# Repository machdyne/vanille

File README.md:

# Vanille Computer

Vanille is an FPGA computer designed by Lone Dynamics Corporation.

This repo will contain schematics, PCB layouts, pinouts, a 3D-printable case, example gateware and documentation.

Find more information on the [Vanille product page](https://machdyne.com/product/vanille-computer/).

## Programming Vanille

Vanille has a JTAG interface and ships with a [DFU bootloader](https://github.com/machdyne/tinydfu-bootloader) that allows the included flash [MMOD](https://machdyne.com/product/mmod) to be programmed over the USB-C port.

### DFU

The DFU bootloader is available for 5 seconds after power-on, issuing a DFU command during this period will stop the boot process until the DFU device is detached. If no command is received the boot process will continue and the user gateware will be loaded.

Install [dfu-util](http://dfu-util.sourceforge.net) (Debian/Ubuntu):

```
$ sudo apt install dfu-util
```

Update the user gateware on the flash MMOD:

```
$ sudo dfu-util -a 0 -D image.bit
```

Detach the DFU device and continue the boot process:

```
$ sudo dfu-util -a 0 -e
```

It is possible to update the bootloader itself using DFU but you shouldn't attempt this unless you have a JTAG programmer (or another method to program the MMOD) available, in case you need to restore the bootloader.

### JTAG

These examples assume you're using a "USB Blaster" JTAG cable, see the header pinout below. You will need to have [openFPGALoader](https://github.com/trabucayre/openFPGALoader) installed.

Program the configuration SRAM:

```
openFPGALoader -c usb-blaster image.bit
```

Program the flash MMOD:

```
openFPGALoader -f -c usb-blaster images/bootloader/tinydfu_vanille.bit
```

## Blinky 

Building the blinky example requires [Yosys](https://github.com/YosysHQ/yosys), [nextpnr-ecp5](https://github.com/YosysHQ/nextpnr) and [Project Trellis](https://github.com/YosysHQ/prjtrellis).

Assuming they are installed, you can simply type `make` to build the gateware, which will be written to output/blinky.bin. You can then use [openFPGALoader](https://github.com/trabucayre/openFPGALoader) or dfu-util to write the gateware to the device.

## Linux

See the [Kakao Linux](https://github.com/machdyne/kakao) repo for the latest instructions.

### Prebuilt Images

Prebuilt gateware capable of running Linux is available in the `images/v2` directory.

### Building Linux-capable Gateware

Please follow the setup instructions in the [linux-on-litex-vexriscv](https://github.com/litex-hub/linux-on-litex-vexriscv) repo and then:

1. Build the Linux-capable gateware:

```
$ cd linux-on-litex-vexriscv
$ ./make.py --board=vanille --dcache-size=64 --icache-size=64 --build
```

NOTE: This may fail, if so:

```
$ cd build/vanille/gateware
```

Edit `vanille.ys` and add the `-abc2` option as shown below:

```
synth_ecp5  -top vanille -abc2
```

Now run:

```
$ bash build_vanille.sh
```

2. Write the gateware to the MMOD using USB DFU:

```
$ sudo dfu-util -a 0 -D vanille.bit
```

3. Copy the device tree binary `../vanille.dtb` to a FAT-formatted MicroSD card.

## JTAG Header

The 3.3V JTAG header can be used to program the FPGA SRAM as well as the MMOD flash memory. It can also be used to provide power (5V) to the board.

```
1 2
3 4
5 6
```

| Pin | Signal |
| --- | ------ |
| 1 | TCK |
| 2 | TDI |
| 3 | TDO |
| 4 | TMS |
| 5 | 5V0 |
| 6 | GND |

## Board Revisions

| Revision | Notes |
| -------- | ----- |
| V0 | Initial prototype |
| V1 | Second prototype; fixes SRAM schematic error; adds LED |
| V2 | Initial production version; fixes another SRAM schematic error |

## License

The contents of this repo are released under the [Lone Dynamics Open License](LICENSE.md) with the following exceptions:

- The KiCad design files contain parts of the [kicad-pmod](https://github.com/mithro/kicad-pmod) library which is released under the [Apache License, Version 2.0](https://www.apache.org/licenses/LICENSE-2.0.html).

- The KiCad design files may contain symbols and footprints released under other licenses; please contact us if we've failed to give proper attribution.

Note: You can use these designs for commercial purposes but we ask that instead of producing exact clones, that you either replace our trademarks and logos with your own or add your own next to ours.

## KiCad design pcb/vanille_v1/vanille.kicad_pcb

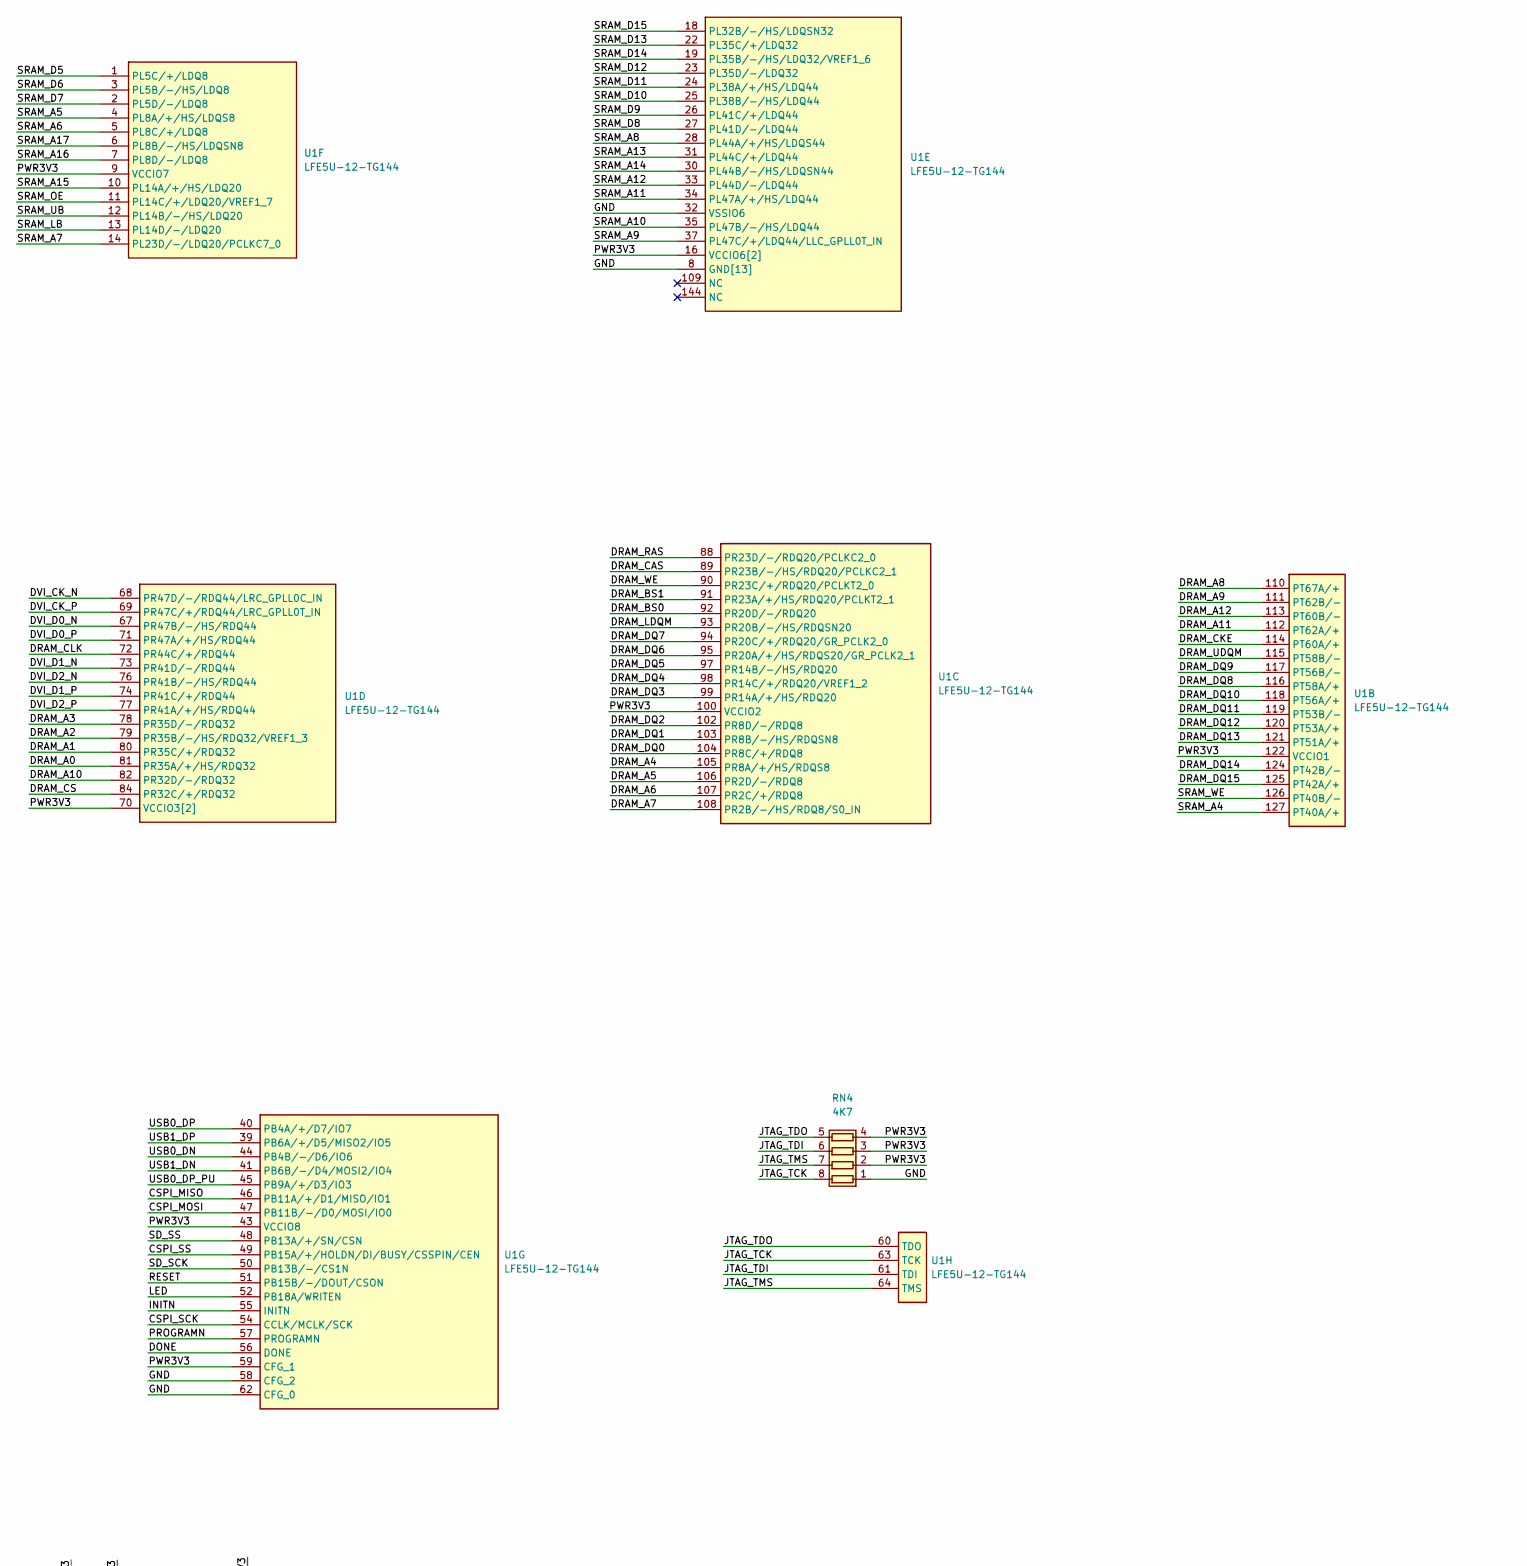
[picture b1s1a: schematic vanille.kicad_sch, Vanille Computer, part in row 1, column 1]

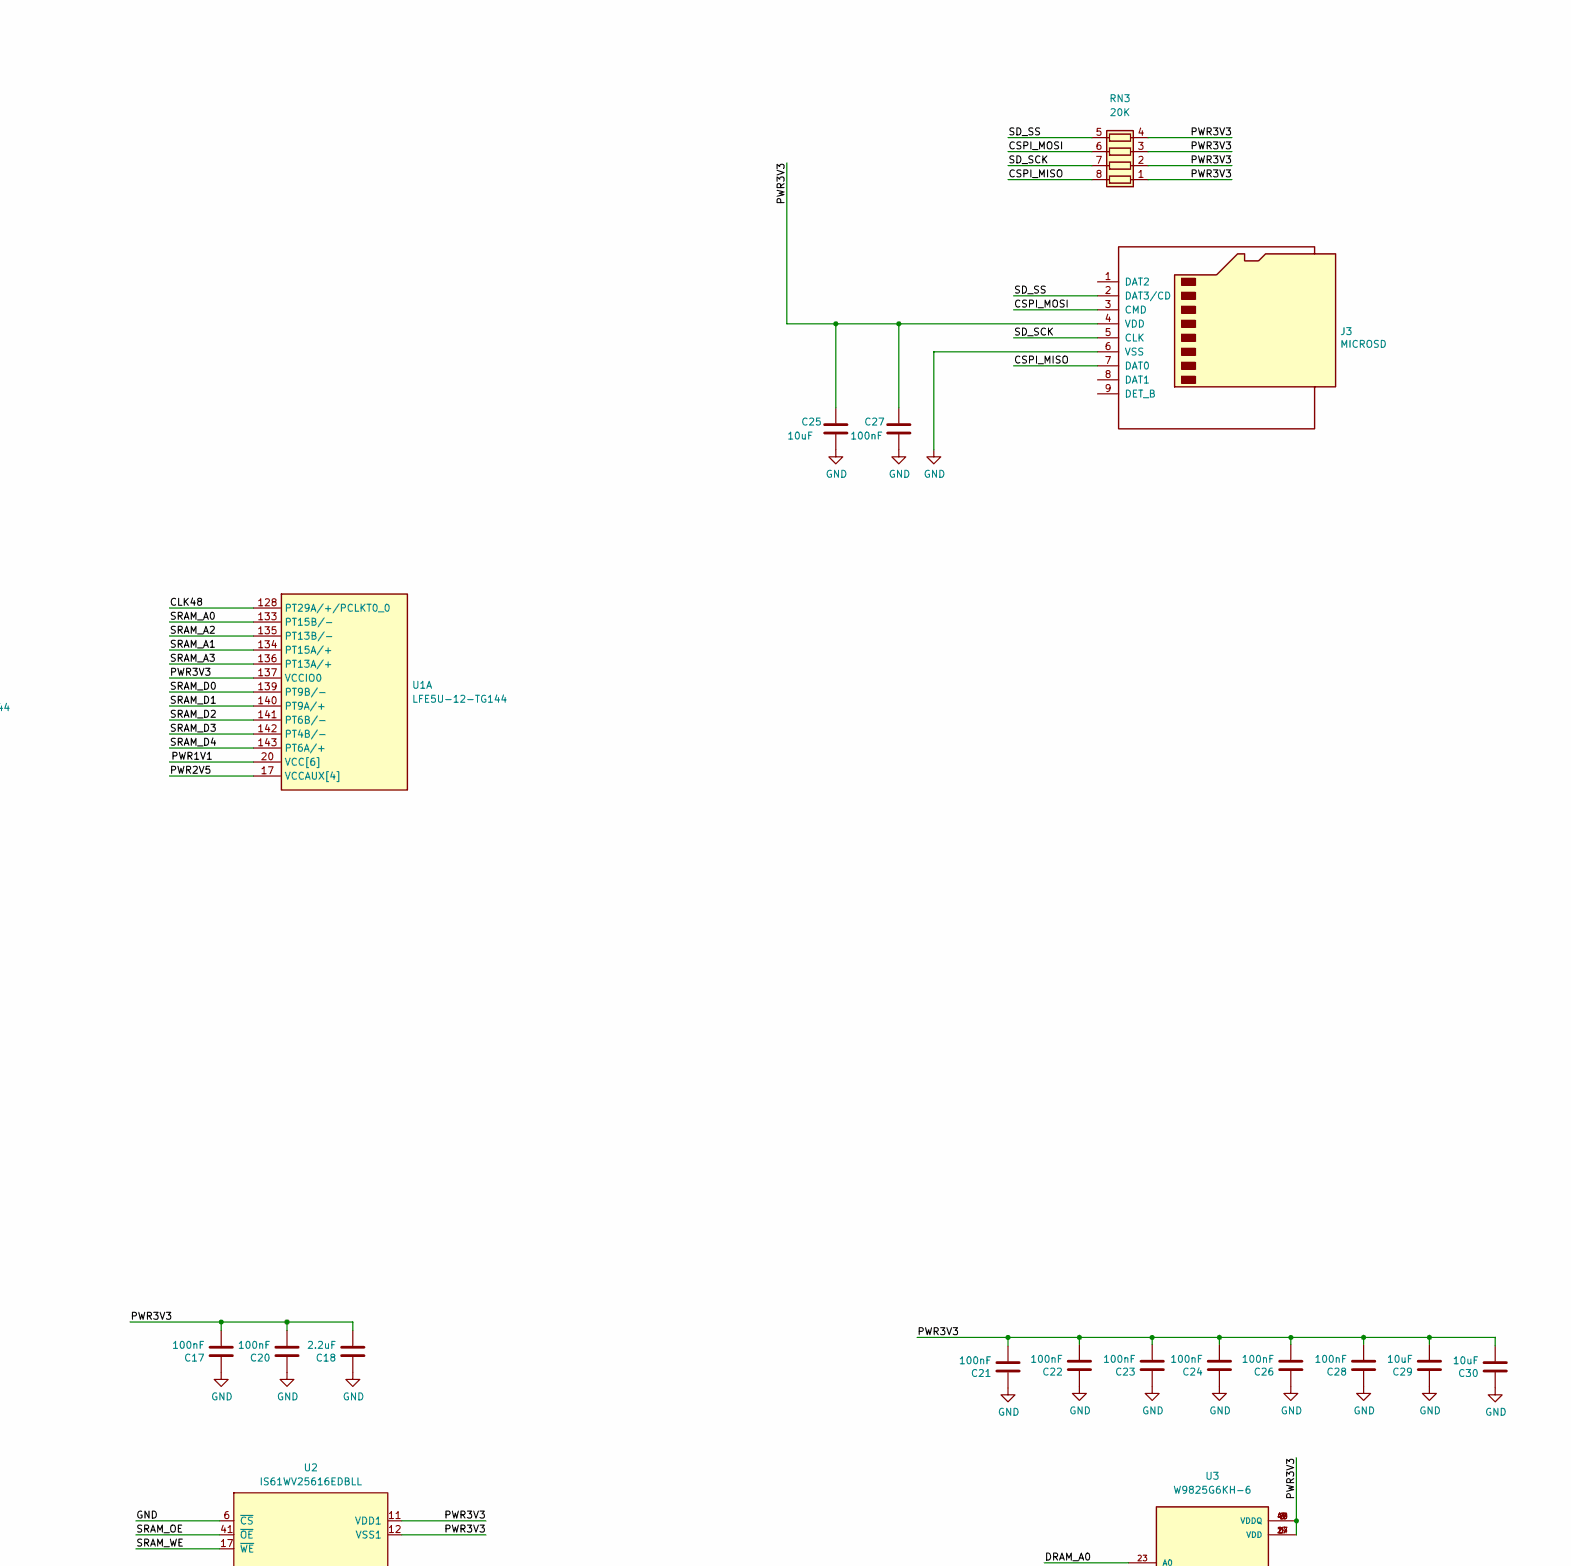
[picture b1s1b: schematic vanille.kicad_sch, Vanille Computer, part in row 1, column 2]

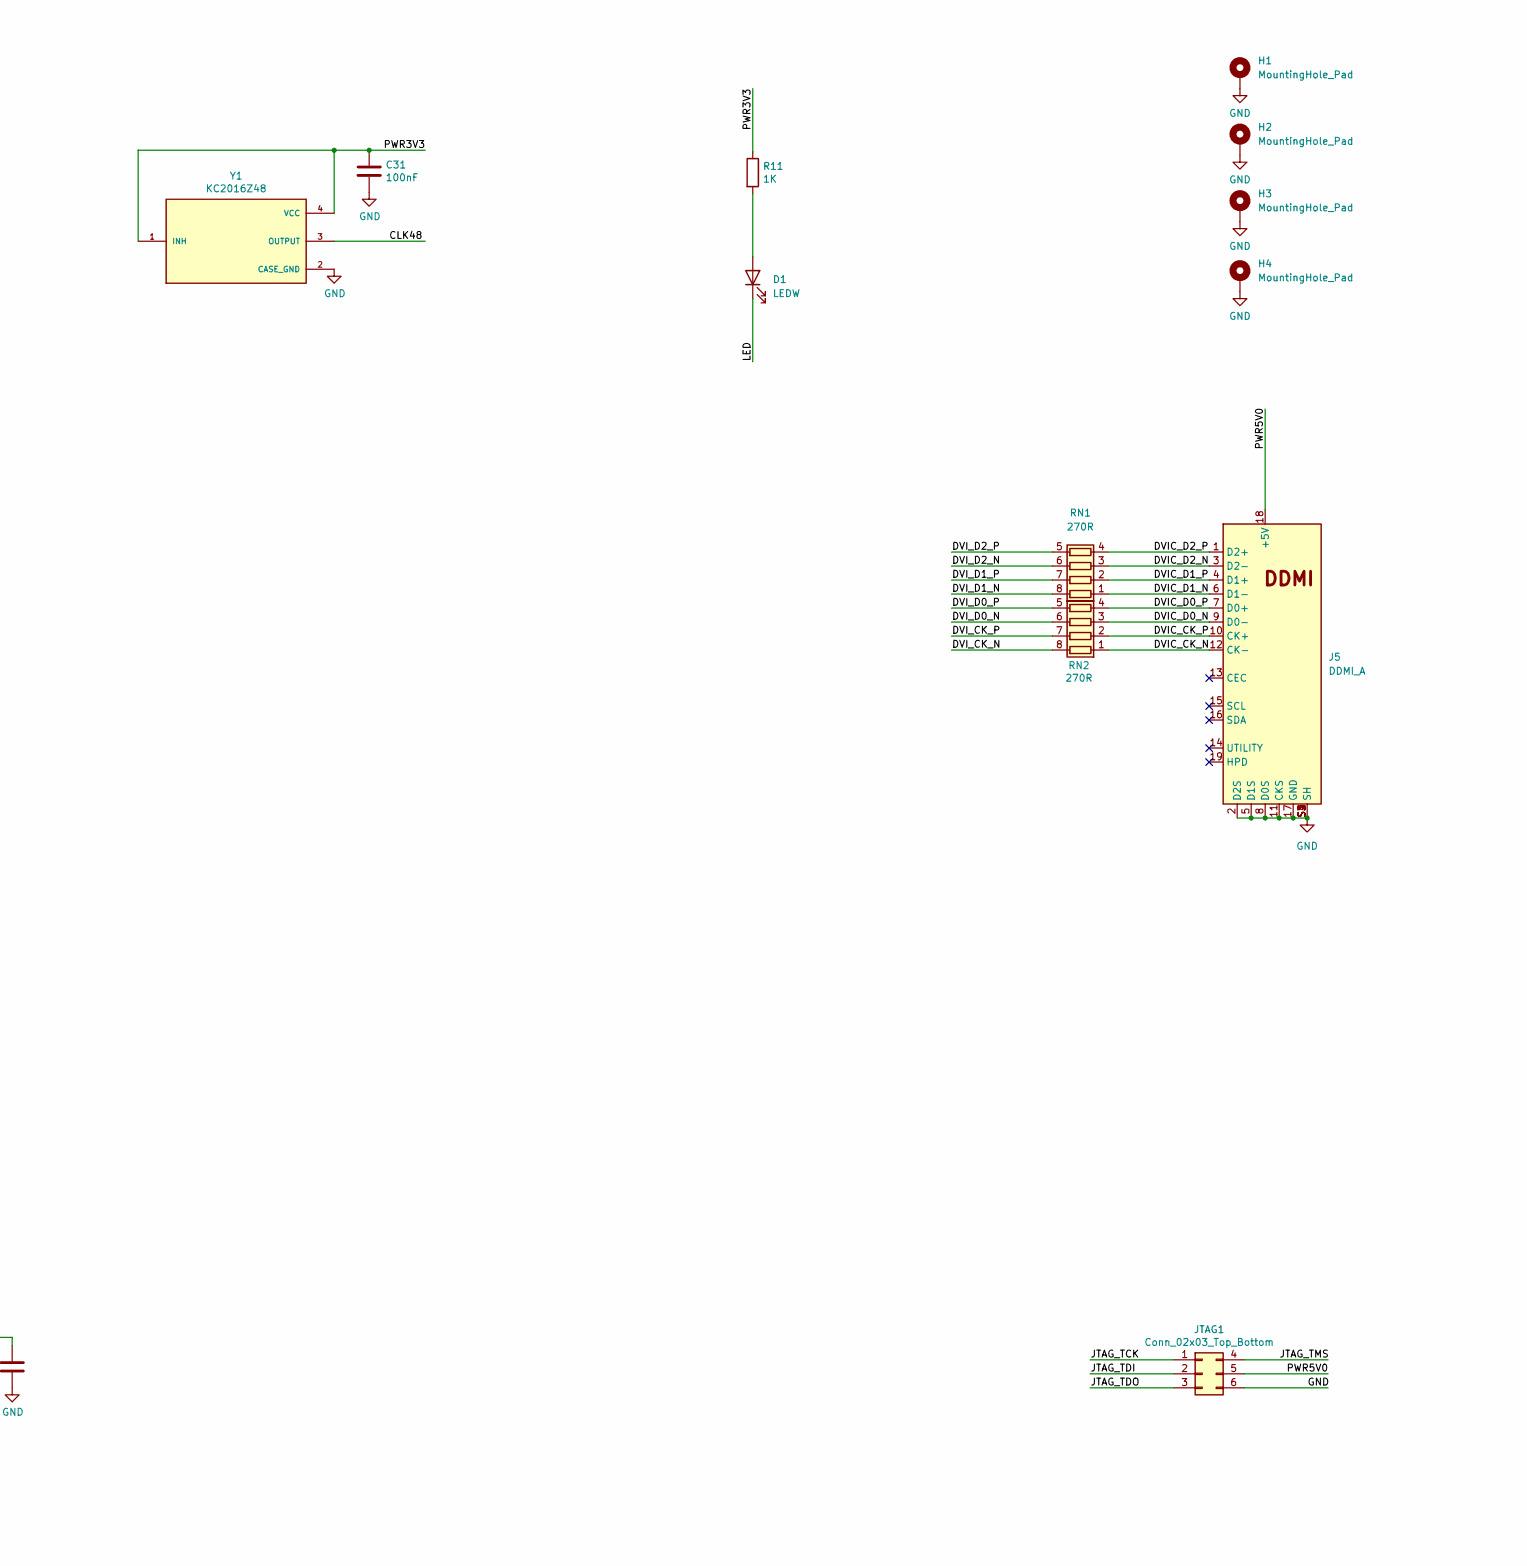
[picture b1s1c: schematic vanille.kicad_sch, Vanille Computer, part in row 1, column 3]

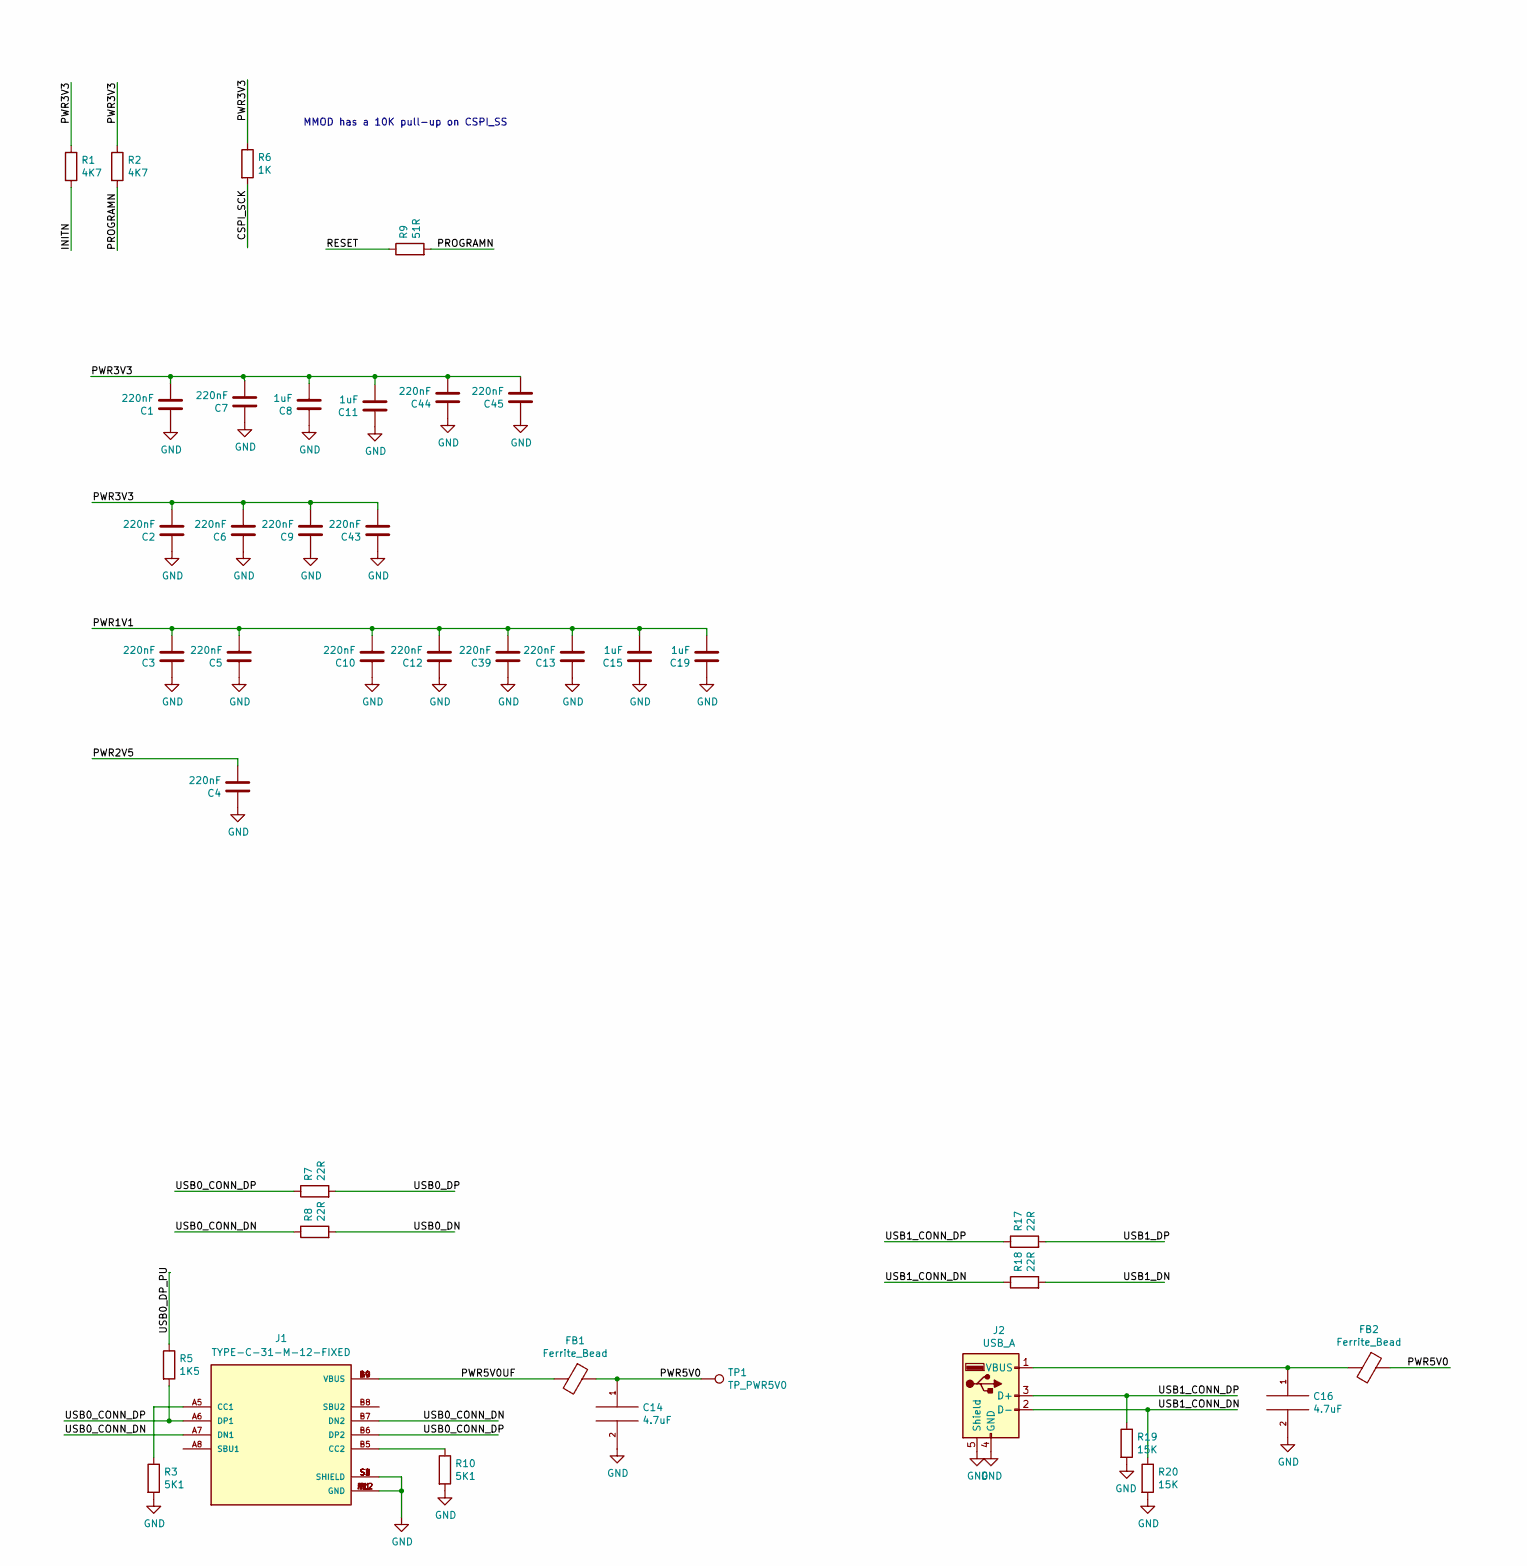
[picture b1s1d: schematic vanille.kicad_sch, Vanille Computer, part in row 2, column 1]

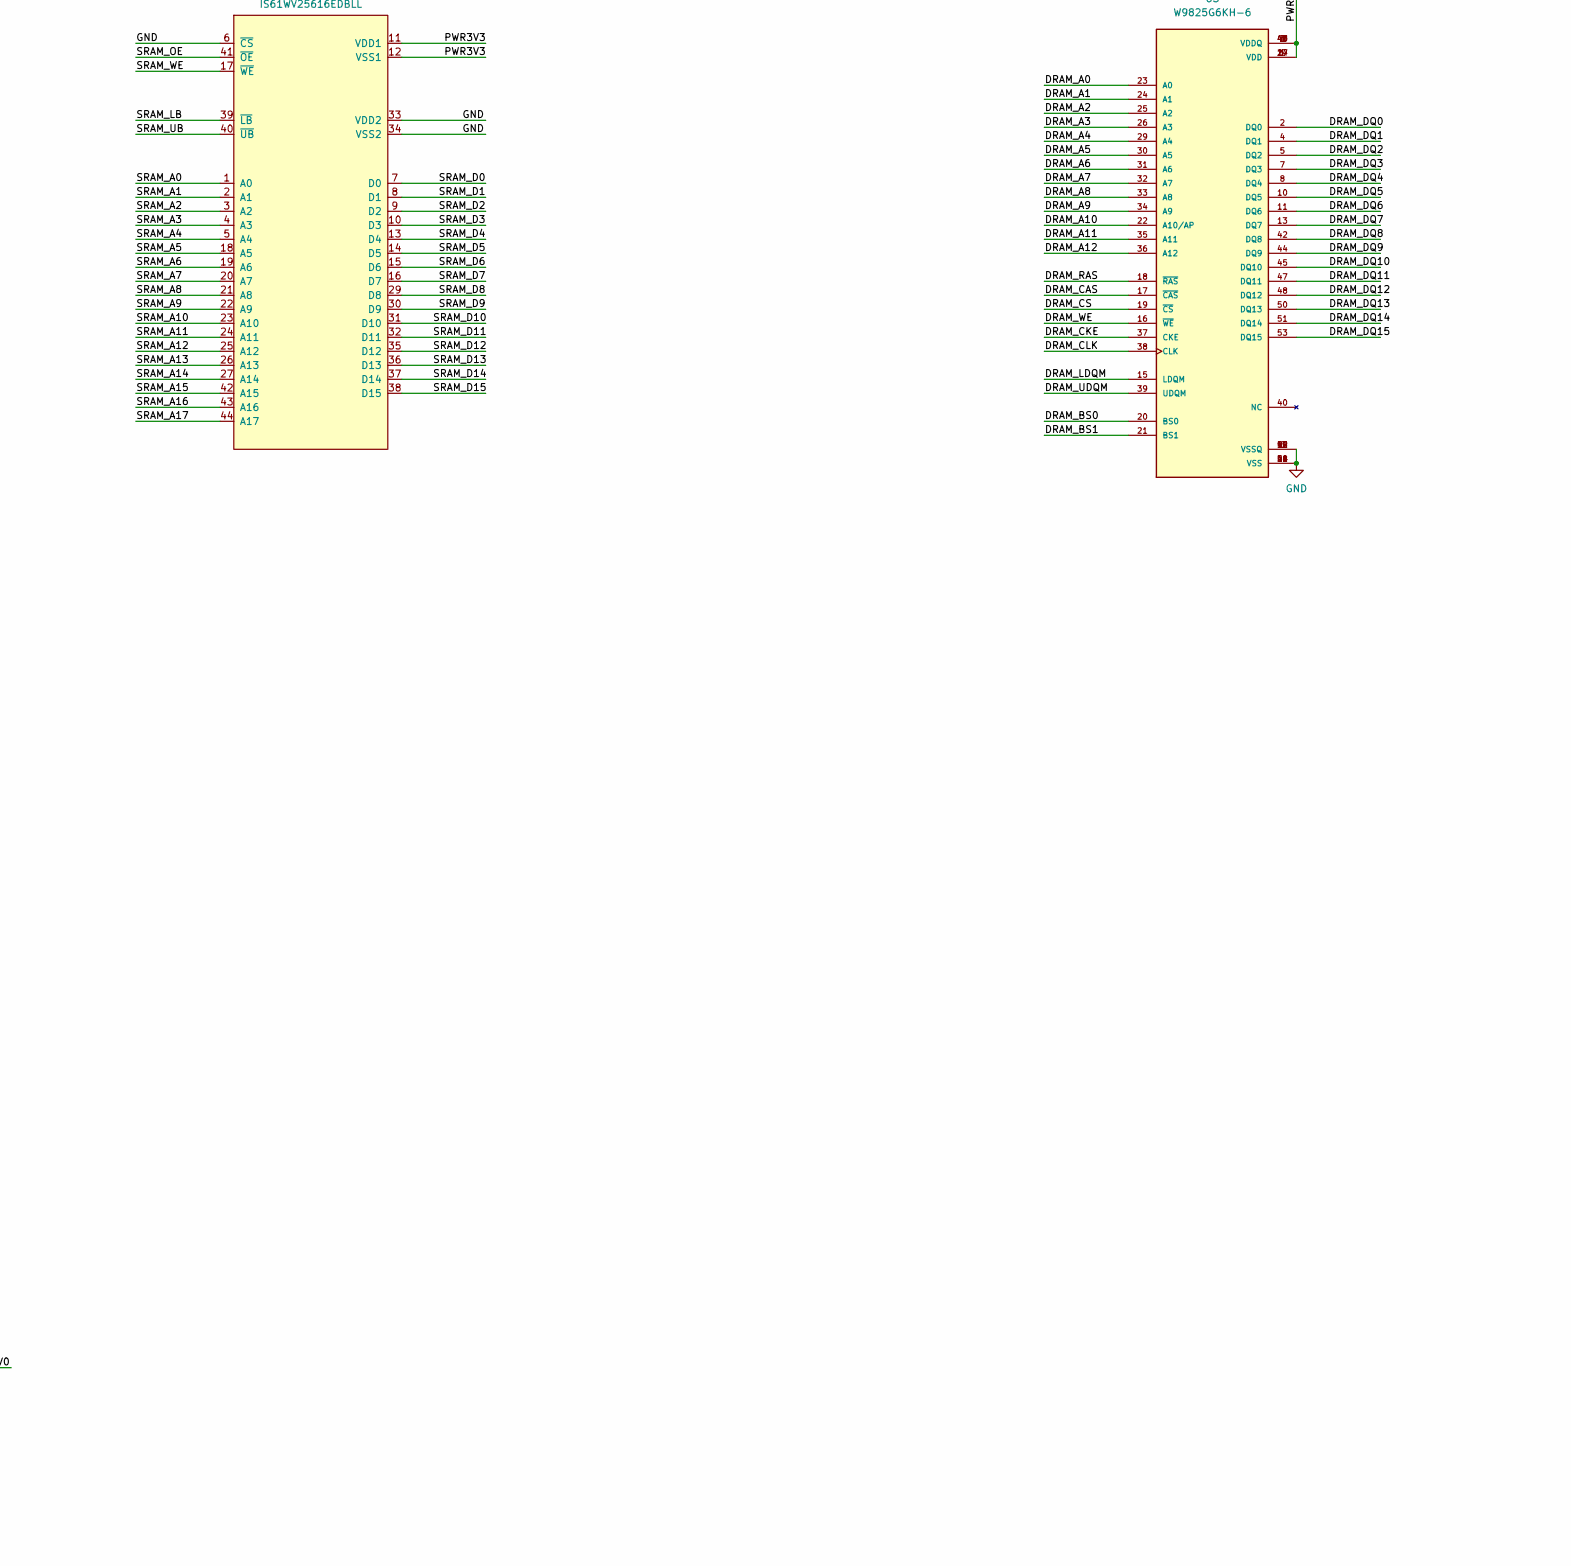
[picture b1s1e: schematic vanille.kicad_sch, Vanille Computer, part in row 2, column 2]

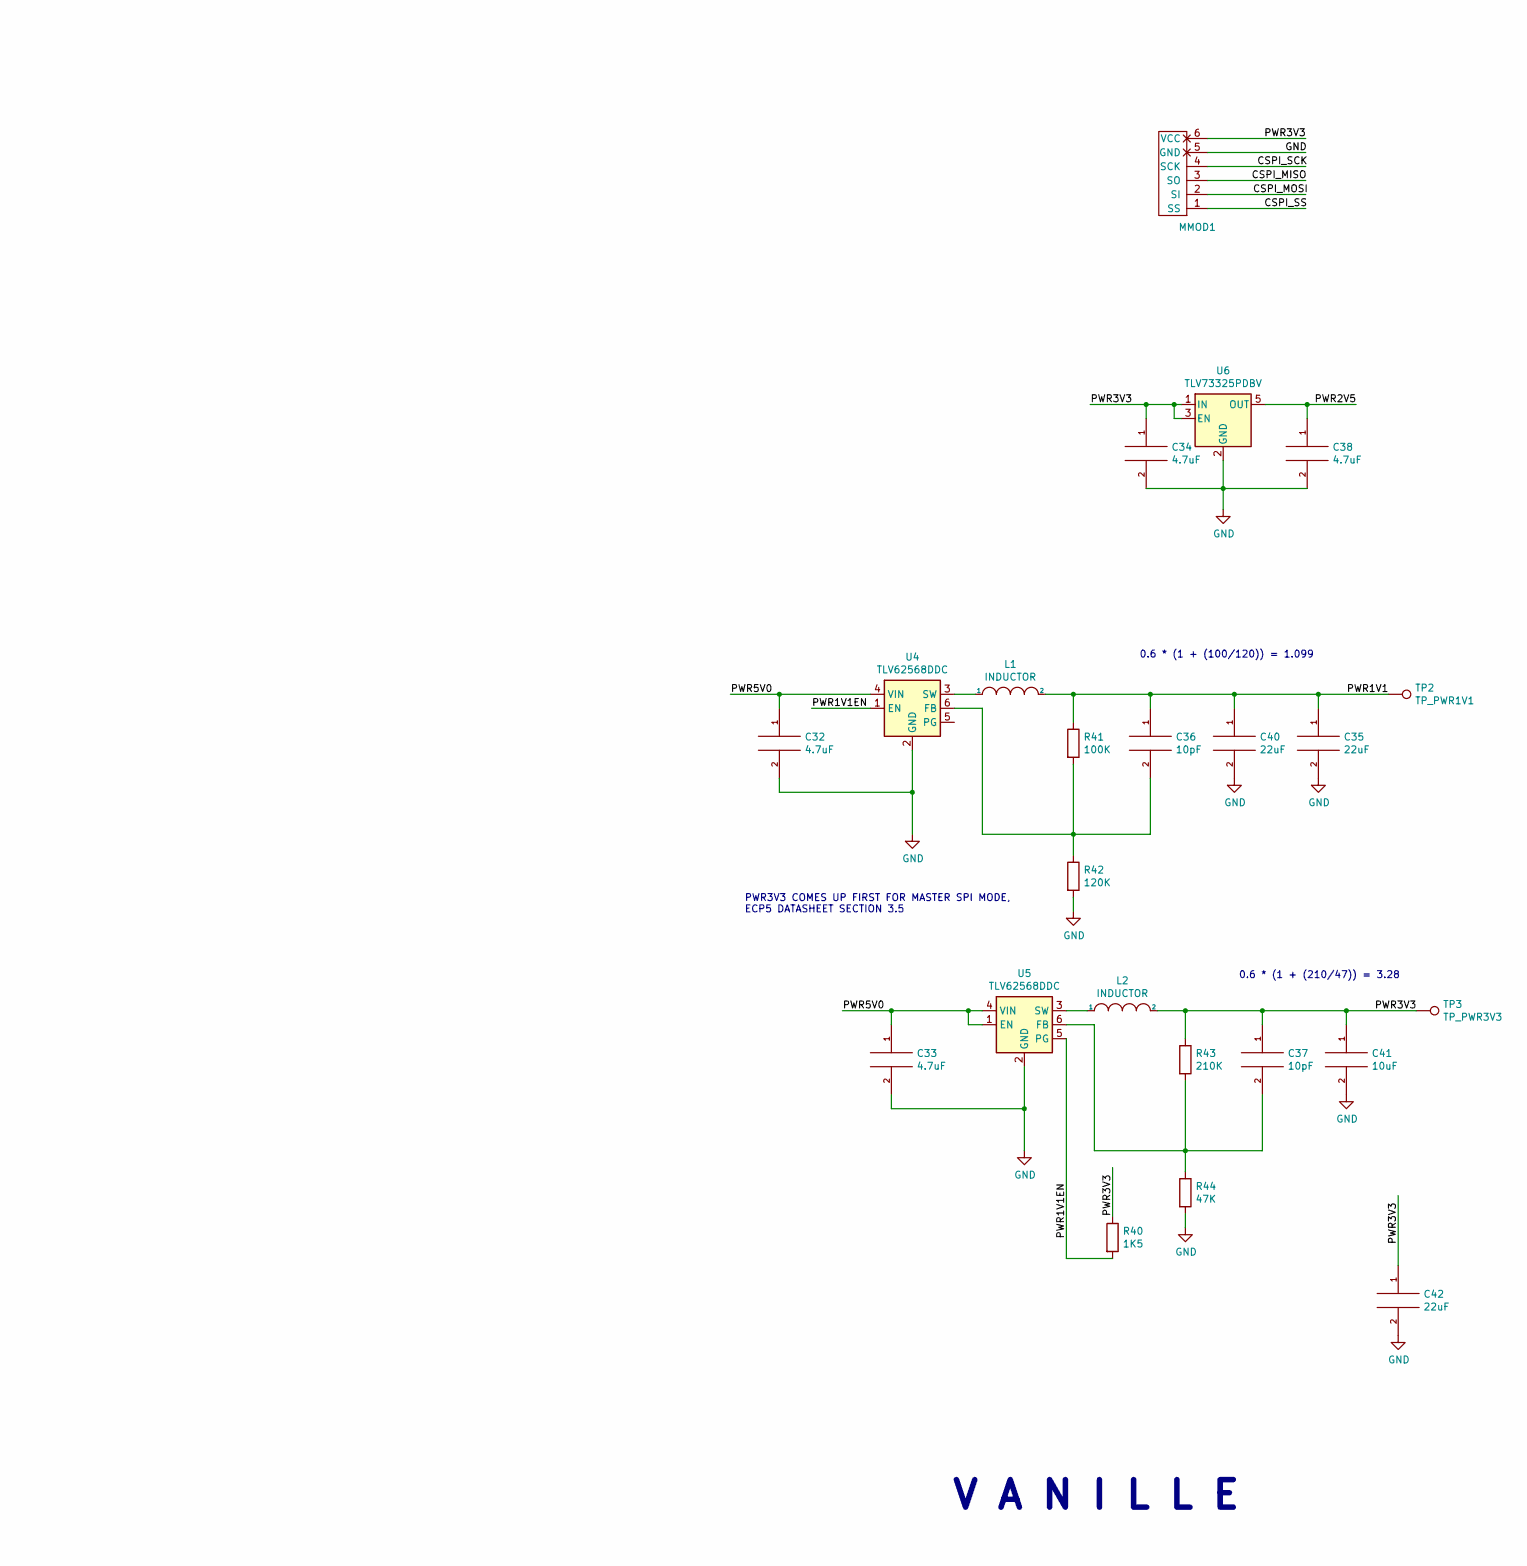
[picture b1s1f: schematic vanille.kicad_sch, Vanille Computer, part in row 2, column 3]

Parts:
C1, C2, C3, C4, C5, C6, C7, C9, C10, C12, C13, C39, C43, C44, C45: 220nF; C_0603_1608Metric
C8, C11, C15, C19: 1uF; C_0603_1608Metric
C14, C16, C32, C33, C34, C38: 4.7uF; C_0603_1608Metric
C17, C20, C21, C22, C23, C24, C26, C27, C28: 100nF; C_0603_1608Metric
C18: 2.2uF; C_0603_1608Metric
C25, C29, C30, C41: 10uF; C_0603_1608Metric
C31: 100nF; R_0603_1608Metric
C35, C40, C42: 22uF; C_0603_1608Metric
C36, C37: 10pF; C_0603_1608Metric
D1: LEDW; LED_0603_1608Metric
FB1, FB2: Ferrite_Bead; R_0603_1608Metric
H1, H2, H3, H4: MountingHole_Pad; MountingHole_3.2mm_M3_Pad
J1: TYPE-C-31-M-12-FIXED; USB_C_Receptacle_HRO_TYPE-C-31-M-12-BIG-PADS; PARTREV A
J2: USB_A; USB_A_Stewart_SS-52100-001_Horizontal
J3: MICROSD; SDCARD
J5: DDMI_A; HDMI_TE_1827059-3-FIXED
JTAG1: Conn_02x03_Top_Bottom; PinHeader_2x03_P2.54mm_Vertical
L1, L2: INDUCTOR; L_0805_2012Metric
MMOD1: PMOD-Device-x1-Type-2-SPI; MMOD_Host_Socket
R1, R2: 4K7; R_0603_1608Metric
R3, R10: 5K1; R_0603_1608Metric
R5, R40: 1K5; R_0603_1608Metric
R6, R11: 1K; R_0603_1608Metric
R7, R8, R17, R18: 22R; R_0603_1608Metric
R9: 51R; R_0603_1608Metric
R19, R20: 15K; R_0603_1608Metric
R41: 100K; R_0603_1608Metric
R42: 120K; R_0603_1608Metric
R43: 210K; R_0603_1608Metric
R44: 47K; R_0603_1608Metric
RN1, RN2: 270R; R_Array_Convex_4x0402
RN3: 20K; R_Array_Convex_4x0402
RN4: 4K7; R_Array_Convex_4x0402
TP1: TP_PWR5V0; TestPoint_THTPad_D1.0mm_Drill0.5mm
TP2: TP_PWR1V1; TestPoint_THTPad_D1.0mm_Drill0.5mm
TP3: TP_PWR3V3; TestPoint_THTPad_D1.0mm_Drill0.5mm
U1: LFE5U-12-TG144
U2: IS61WV25616EDBLL; TSOP-II-44_10.16x18.41mm_P0.8mm
U3: W9825G6KH-6; SOP80P1176X120-54N; PARTREV A05
U4, U5: TLV62568DDC; SOT-23-6
U6: TLV73325PDBV; SOT-23-5
Y1: KC2016Z48; OSC_KC2016Z13.5600C1KX00; PARTREV November 2020

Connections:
/CLK48: U1.128 (PT29A/+/PCLKT0_0), Y1.3 (OUTPUT)
/CSPI_MISO: J3.7 (DAT0), MMOD1.3 (SO), RN3.8 (R1.2), U1.46 (PB11A/+/D1/MISO/IO1)
/CSPI_MOSI: J3.3 (CMD), MMOD1.2 (SI), RN3.6 (R3.2), U1.47 (PB11B/-/D0/MOSI/IO0)
/CSPI_SCK: MMOD1.4 (SCK), R6.2, U1.54 (CCLK/MCLK/SCK)
/CSPI_SS: MMOD1.1 (SS), U1.49 (PB15A/+/HOLDN/DI/BUSY/CSSPIN/CEN)
/DONE: U1.56 (DONE)
/DRAM_A0: U1.81 (PR35A/+/HS/RDQ32), U3.23 (A0)
/DRAM_A1: U1.80 (PR35C/+/RDQ32), U3.24 (A1)
/DRAM_A2: U1.79 (PR35B/-/HS/RDQ32/VREF1_3), U3.25 (A2)
/DRAM_A3: U1.78 (PR35D/-/RDQ32), U3.26 (A3)
/DRAM_A4: U1.105 (PR8A/+/HS/RDQS8), U3.29 (A4)
/DRAM_A5: U1.106 (PR2D/-/RDQ8), U3.30 (A5)
/DRAM_A6: U1.107 (PR2C/+/RDQ8), U3.31 (A6)
/DRAM_A7: U1.108 (PR2B/-/HS/RDQ8/S0_IN), U3.32 (A7)
/DRAM_A8: U1.110 (PT67A/+), U3.33 (A8)
/DRAM_A9: U1.111 (PT62B/-), U3.34 (A9)
/DRAM_A10: U1.82 (PR32D/-/RDQ32), U3.22 (A10/AP)
/DRAM_A11: U1.112 (PT62A/+), U3.35 (A11)
/DRAM_A12: U1.113 (PT60B/-), U3.36 (A12)
/DRAM_BS0: U1.92 (PR20D/-/RDQ20), U3.20 (BS0)
/DRAM_BS1: U1.91 (PR23A/+/HS/RDQ20/PCLKT2_1), U3.21 (BS1)
/DRAM_CAS: U1.89 (PR23B/-/HS/RDQ20/PCLKC2_1), U3.17 (~CAS)
/DRAM_CKE: U1.114 (PT60A/+), U3.37 (CKE)
/DRAM_CLK: U1.72 (PR44C/+/RDQ44), U3.38 (CLK)
/DRAM_CS: U1.84 (PR32C/+/RDQ32), U3.19 (~CS)
/DRAM_DQ0: U1.104 (PR8C/+/RDQ8), U3.2 (DQ0)
/DRAM_DQ1: U1.103 (PR8B/-/HS/RDQSN8), U3.4 (DQ1)
/DRAM_DQ2: U1.102 (PR8D/-/RDQ8), U3.5 (DQ2)
/DRAM_DQ3: U1.99 (PR14A/+/HS/RDQ20), U3.7 (DQ3)
/DRAM_DQ4: U1.98 (PR14C/+/RDQ20/VREF1_2), U3.8 (DQ4)
/DRAM_DQ5: U1.97 (PR14B/-/HS/RDQ20), U3.10 (DQ5)
/DRAM_DQ6: U1.95 (PR20A/+/HS/RDQS20/GR_PCLK2_1), U3.11 (DQ6)
/DRAM_DQ7: U1.94 (PR20C/+/RDQ20/GR_PCLK2_0), U3.13 (DQ7)
/DRAM_DQ8: U1.116 (PT58A/+), U3.42 (DQ8)
/DRAM_DQ9: U1.117 (PT56B/-), U3.44 (DQ9)
/DRAM_DQ10: U1.118 (PT56A/+), U3.45 (DQ10)
/DRAM_DQ11: U1.119 (PT53B/-), U3.47 (DQ11)
/DRAM_DQ12: U1.120 (PT53A/+), U3.48 (DQ12)
/DRAM_DQ13: U1.121 (PT51A/+), U3.50 (DQ13)
/DRAM_DQ14: U1.124 (PT42B/-), U3.51 (DQ14)
/DRAM_DQ15: U1.125 (PT42A/+), U3.53 (DQ15)
/DRAM_LDQM: U1.93 (PR20B/-/HS/RDQSN20), U3.15 (LDQM)
/DRAM_RAS: U1.88 (PR23D/-/RDQ20/PCLKC2_0), U3.18 (~RAS)
/DRAM_UDQM: U1.115 (PT58B/-), U3.39 (UDQM)
/DRAM_WE: U1.90 (PR23C/+/RDQ20/PCLKT2_0), U3.16 (~WE)
/DVIC_CK_N: J5.12 (CK-), RN2.1 (R1.1)
/DVIC_CK_P: J5.10 (CK+), RN2.2 (R2.1)
/DVIC_D0_N: J5.9 (D0-), RN2.3 (R3.1)
/DVIC_D0_P: J5.7 (D0+), RN2.4 (R4.1)
/DVIC_D1_N: J5.6 (D1-), RN1.1 (R1.1)
/DVIC_D1_P: J5.4 (D1+), RN1.2 (R2.1)
/DVIC_D2_N: J5.3 (D2-), RN1.3 (R3.1)
/DVIC_D2_P: J5.1 (D2+), RN1.4 (R4.1)
/DVI_CK_N: RN2.8 (R1.2), U1.68 (PR47D/-/RDQ44/LRC_GPLL0C_IN)
/DVI_CK_P: RN2.7 (R2.2), U1.69 (PR47C/+/RDQ44/LRC_GPLL0T_IN)
/DVI_D0_N: RN2.6 (R3.2), U1.67 (PR47B/-/HS/RDQ44)
/DVI_D0_P: RN2.5 (R4.2), U1.71 (PR47A/+/HS/RDQ44)
/DVI_D1_N: RN1.8 (R1.2), U1.73 (PR41D/-/RDQ44)
/DVI_D1_P: RN1.7 (R2.2), U1.74 (PR41C/+/RDQ44)
/DVI_D2_N: RN1.6 (R3.2), U1.76 (PR41B/-/HS/RDQ44)
/DVI_D2_P: RN1.5 (R4.2), U1.77 (PR41A/+/HS/RDQ44)
/INITN: R1.2, U1.55 (INITN)
/JTAG_TCK: JTAG1.1, RN4.8 (R1.2), U1.63 (TCK)
/JTAG_TDI: JTAG1.2, RN4.6 (R3.2), U1.61 (TDI)
/JTAG_TDO: JTAG1.3, RN4.5 (R4.2), U1.60 (TDO)
/JTAG_TMS: JTAG1.4, RN4.7 (R2.2), U1.64 (TMS)
/LED: D1.1 (K), U1.52 (PB18A/WRITEN)
/PROGRAMN: R2.2, R9.2, U1.57 (PROGRAMN)
/PWR1V1: C3.2, C5.2, C10.2, C12.2, C13.2, C15.2, C19.2, C35.1, C36.1, C39.2, C40.1, L1.2, R41.1, TP2.1, U1.20 (VCC[6]), U1.29 (VCC[6]), U1.38 (VCC[6]), U1.66 (VCC[6]), U1.83 (VCC[6]), U1.130 (VCC[6])
/PWR1V1EN: R40.2, U4.1 (EN), U5.5 (PG)
/PWR2V5: C4.2, C38.1, U1.17 (VCCAUX[4]), U1.53 (VCCAUX[4]), U1.96 (VCCAUX[4]), U1.132 (VCCAUX[4]), U6.5 (OUT)
/PWR3V3: C1.2, C2.2, C6.2, C7.2, C8.2, C9.2, C11.2, C17.2, C18.2, C20.2, C21.2, C22.2, C23.2, C24.2, C25.1, C26.2, C27.1, C28.2, C29.2, C30.2, C31.1, C34.1, C37.1, C41.1, C42.1, C43.2, C44.2, C45.2, J3.4 (VDD), L2.2, MMOD1.6 (VCC), R1.1, R2.1, R6.1, R11.1, R40.1, R43.1, RN3.1 (R1.1), RN3.2 (R2.1), RN3.3 (R3.1), RN3.4 (R4.1), RN4.2 (R2.1), RN4.3 (R3.1), RN4.4 (R4.1), TP3.1, U1.9 (VCCIO7), U1.16 (VCCIO6[2]), U1.36 (VCCIO6[2]), U1.43 (VCCIO8), U1.59 (CFG_1), U1.70 (VCCIO3[2]), U1.86 (VCCIO3[2]), U1.100 (VCCIO2), U1.122 (VCCIO1), U1.137 (VCCIO0), U2.11 (VDD1), U2.12 (VSS1), U3.1 (VDD), U3.3 (VDDQ), U3.9 (VDDQ), U3.14 (VDD), U3.27 (VDD), U3.43 (VDDQ), U3.49 (VDDQ), U6.1 (IN), U6.3 (EN), Y1.1 (INH), Y1.4 (VCC)
/PWR5V0: C14.1, C32.1, C33.1, FB1.1, FB2.1, J5.18 (+5V), JTAG1.5, TP1.1, U4.4 (VIN), U5.1 (EN), U5.4 (VIN)
/PWR5V0UF: FB1.2, J1.A4 (VBUS), J1.A9 (VBUS), J1.B4 (VBUS), J1.B9 (VBUS)
/RESET: R9.1, U1.51 (PB15B/-/DOUT/CSON)
/SD_SCK: J3.5 (CLK), RN3.7 (R2.2), U1.50 (PB13B/-/CS1N)
/SD_SS: J3.2 (DAT3/CD), RN3.5 (R4.2), U1.48 (PB13A/+/SN/CSN)
/SRAM_A0: U1.133 (PT15B/-), U2.1 (A0)
/SRAM_A1: U1.134 (PT15A/+), U2.2 (A1)
/SRAM_A2: U1.135 (PT13B/-), U2.3 (A2)
/SRAM_A3: U1.136 (PT13A/+), U2.4 (A3)
/SRAM_A4: U1.127 (PT40A/+), U2.5 (A4)
/SRAM_A5: U1.4 (PL8A/+/HS/LDQS8), U2.18 (A5)
/SRAM_A6: U1.5 (PL8C/+/LDQ8), U2.19 (A6)
/SRAM_A7: U1.14 (PL23D/-/LDQ20/PCLKC7_0), U2.20 (A7)
/SRAM_A8: U1.28 (PL44A/+/HS/LDQS44), U2.21 (A8)
/SRAM_A9: U1.37 (PL47C/+/LDQ44/LLC_GPLL0T_IN), U2.22 (A9)
/SRAM_A10: U1.35 (PL47B/-/HS/LDQ44), U2.23 (A10)
/SRAM_A11: U1.34 (PL47A/+/HS/LDQ44), U2.24 (A11)
/SRAM_A12: U1.33 (PL44D/-/LDQ44), U2.25 (A12)
/SRAM_A13: U1.31 (PL44C/+/LDQ44), U2.26 (A13)
/SRAM_A14: U1.30 (PL44B/-/HS/LDQSN44), U2.27 (A14)
/SRAM_A15: U1.10 (PL14A/+/HS/LDQ20), U2.42 (A15)
/SRAM_A16: U1.7 (PL8D/-/LDQ8), U2.43 (A16)
/SRAM_A17: U1.6 (PL8B/-/HS/LDQSN8), U2.44 (A17)
/SRAM_D0: U1.139 (PT9B/-), U2.7 (D0)
/SRAM_D1: U1.140 (PT9A/+), U2.8 (D1)
/SRAM_D2: U1.141 (PT6B/-), U2.9 (D2)
/SRAM_D3: U1.142 (PT4B/-), U2.10 (D3)
/SRAM_D4: U1.143 (PT6A/+), U2.13 (D4)
/SRAM_D5: U1.1 (PL5C/+/LDQ8), U2.14 (D5)
/SRAM_D6: U1.3 (PL5B/-/HS/LDQ8), U2.15 (D6)
/SRAM_D7: U1.2 (PL5D/-/LDQ8), U2.16 (D7)
/SRAM_D8: U1.27 (PL41D/-/LDQ44), U2.29 (D8)
/SRAM_D9: U1.26 (PL41C/+/LDQ44), U2.30 (D9)
/SRAM_D10: U1.25 (PL38B/-/HS/LDQ44), U2.31 (D10)
/SRAM_D11: U1.24 (PL38A/+/HS/LDQ44), U2.32 (D11)
/SRAM_D12: U1.23 (PL35D/-/LDQ32), U2.35 (D12)
/SRAM_D13: U1.22 (PL35C/+/LDQ32), U2.36 (D13)
/SRAM_D14: U1.19 (PL35B/-/HS/LDQ32/VREF1_6), U2.37 (D14)
/SRAM_D15: U1.18 (PL32B/-/HS/LDQSN32), U2.38 (D15)
/SRAM_LB: U1.13 (PL14D/-/LDQ20), U2.39 (~LB)
/SRAM_OE: U1.11 (PL14C/+/LDQ20/VREF1_7), U2.41 (~OE)
/SRAM_UB: U1.12 (PL14B/-/HS/LDQ20), U2.40 (~UB)
/SRAM_WE: U1.126 (PT40B/-), U2.17 (~WE)
/USB0_CONN_DN: J1.A7 (DN1), J1.B7 (DN2), R8.1
/USB0_CONN_DP: J1.A6 (DP1), J1.B6 (DP2), R5.2, R7.1
/USB0_DN: R8.2, U1.44 (PB4B/-/D6/IO6)
/USB0_DP: R7.2, U1.40 (PB4A/+/D7/IO7)
/USB0_DP_PU: R5.1, U1.45 (PB9A/+/D3/IO3)
/USB1_CONN_DN: J2.2 (D-), R18.1, R20.1
/USB1_CONN_DP: J2.3 (D+), R17.1, R19.1
/USB1_DN: R18.2, U1.41 (PB6B/-/D4/MOSI2/IO4)
/USB1_DP: R17.2, U1.39 (PB6A/+/D5/MISO2/IO5)
GND: C1.1, C2.1, C3.1, C4.1, C5.1, C6.1, C7.1, C8.1, C9.1, C10.1, C11.1, C12.1, C13.1, C14.2, C15.1, C16.2, C17.1, C18.1, C19.1, C20.1, C21.1, C22.1, C23.1, C24.1, C25.2, C26.1, C27.2, C28.1, C29.1, C30.1, C31.2, C32.2, C33.2, C34.2, C35.2, C38.2, C39.1, C40.2, C41.2, C42.2, C43.1, C44.1, C45.1, H1.1, H2.1, H3.1, H4.1, J1.A1 (GND), J1.A12 (GND), J1.B1 (GND), J1.B12 (GND), J1.S1 (SHIELD), J1.S2 (SHIELD), J1.S3 (SHIELD), J1.S4 (SHIELD), J2.4 (GND), J2.5 (Shield), J3.6 (VSS), J5.2 (D2S), J5.5 (D1S), J5.8 (D0S), J5.11 (CKS), J5.17 (GND), J5.S1 (SH), J5.S2 (SH), J5.S3 (SH), J5.S4 (SH), JTAG1.6, MMOD1.5 (GND), R3.2, R10.2, R19.2, R20.2, R42.2, R44.2, RN4.1 (R1.1), U1.8 (GND[13]), U1.15 (GND[13]), U1.21 (GND[13]), U1.32 (VSSIO6), U1.42 (GND[13]), U1.58 (CFG_2), U1.62 (CFG_0), U1.65 (GND[13]), U1.75 (GND[13]), U1.85 (GND[13]), U1.87 (GND[13]), U1.101 (GND[13]), U1.123 (GND[13]), U1.129 (GND[13]), U1.131 (GND[13]), U1.138 (GND[13]), U2.6 (~CS), U2.33 (VDD2), U2.34 (VSS2), U3.6 (VSSQ), U3.12 (VSSQ), U3.28 (VSS), U3.41 (VSS), U3.46 (VSSQ), U3.52 (VSSQ), U3.54 (VSS), U4.2 (GND), U5.2 (GND), U6.2 (GND), Y1.2 (CASE_GND)
unnamed: C16.1, FB2.2, J2.1 (VBUS)
unnamed: C36.2, R41.2, R42.1, U4.6 (FB)
unnamed: C37.2, R43.2, R44.1, U5.6 (FB)
unnamed: D1.2 (A), R11.2
unnamed: J1.A5 (CC1), R3.1
unnamed: J1.B5 (CC2), R10.1
unnamed: L1.1, U4.3 (SW)
unnamed: L2.1, U5.3 (SW)

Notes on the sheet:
V A N I L L E
PWR3V3 COMES UP FIRST FOR MASTER SPI MODE, ECP5 DATASHEET SECTION 3.5
0.6 * (1 + (210/47)) = 3.28
MMOD has a 10K pull-up on CSPI_SS
0.6 * (1 + (100/120)) = 1.099

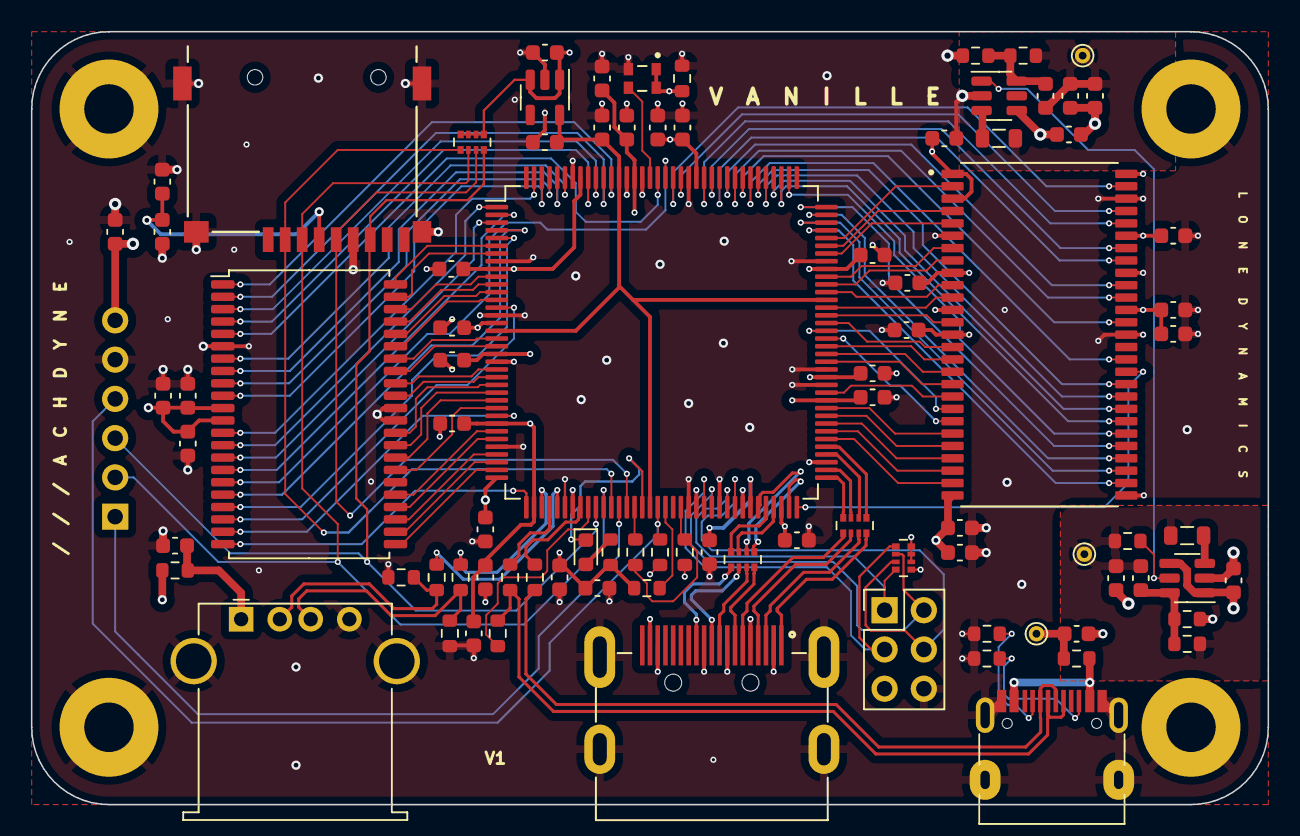
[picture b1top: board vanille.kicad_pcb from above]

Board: 4 copper layers, 80.0 x 50.0 mm, 93 parts (1 on the bottom side), 132 nets.

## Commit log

2024-02-07 add render
2024-02-11 add fpga symbol/scripts
2024-02-11 add v0 pcb
2024-02-21 add v1 pcb
2024-02-25 add v1 schematic pdf
2024-02-29 add v2
2024-02-29 rename files
2024-03-13 add dfu bootloader
2024-03-13 latest schematics pdf

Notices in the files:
pcb/vanille_v0/vanille.kicad_sch:
Copyright © 2023 Lone Dynamics Corporation. All rights reserved.
